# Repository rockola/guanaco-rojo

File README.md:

# guanaco-rojo
Guanaco Rojo PCB, yet another Red Llama clone

* v0.1: initial import, complete, unverified
* v0.2: pcb rerouted for 9 mm pots
* v0.3: SMD 4049 IC

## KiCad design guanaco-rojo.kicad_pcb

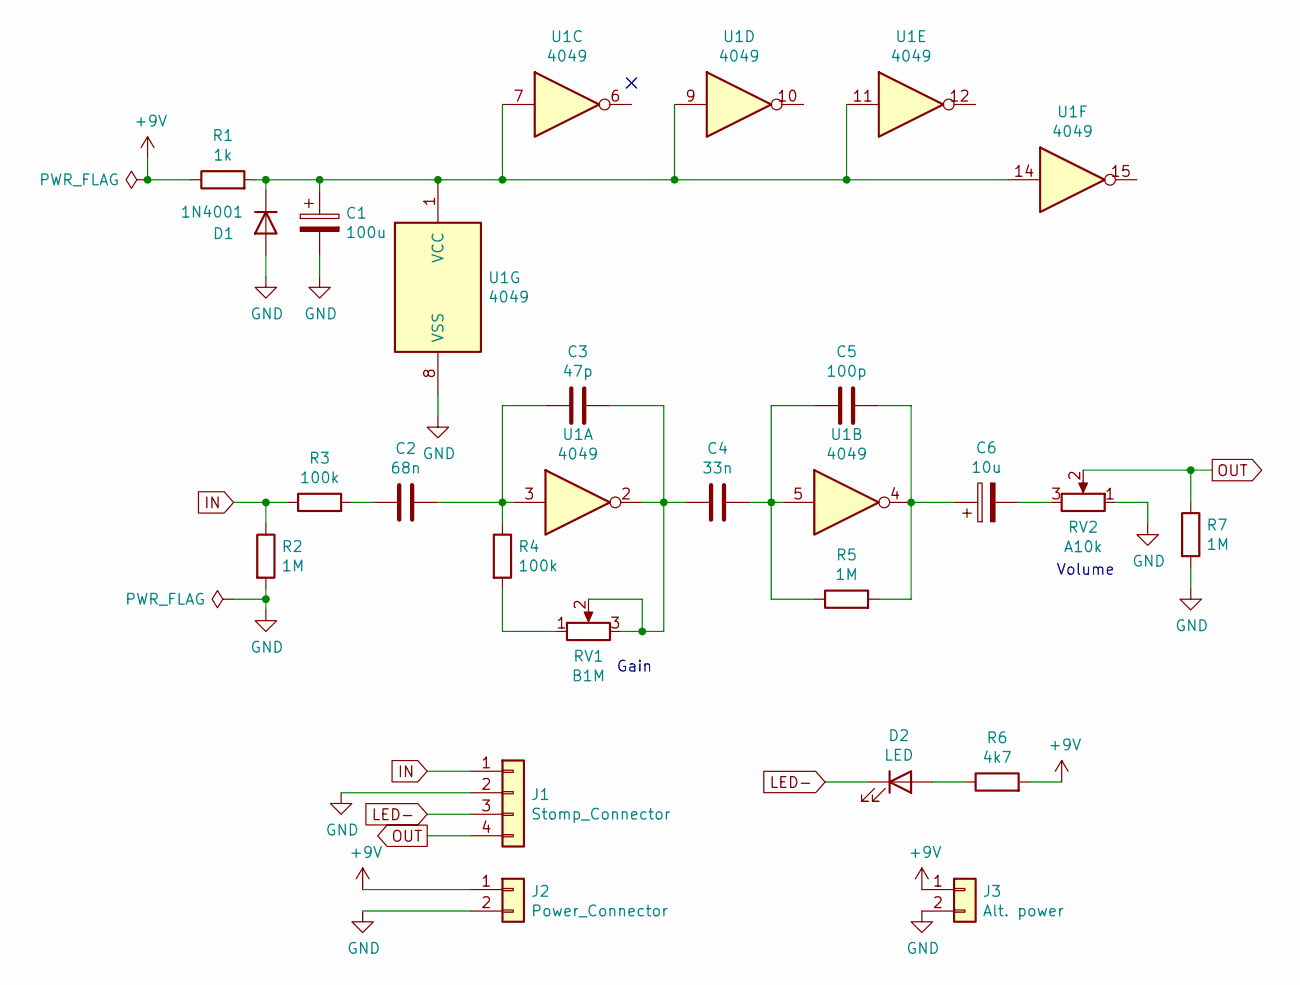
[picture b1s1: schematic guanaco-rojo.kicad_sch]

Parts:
C1: 100u; CP_Radial_D6.3mm_P2.50mm
C2: 68n; C_Rect_L7.0mm_W2.5mm_P5.00mm
C3: 47p; C_Disc_D5.0mm_W2.5mm_P5.00mm
C4: 33n; C_Rect_L7.0mm_W2.5mm_P5.00mm
C5: 100p; C_Disc_D5.0mm_W2.5mm_P5.00mm
C6: 10u; CP_Radial_D6.3mm_P2.50mm
D1: 1N4001; D_DO-41_SOD81_P7.62mm_Horizontal
D2: LED; LED_D5.0mm
J1: Stomp_Connector; Stomp_4pin
J2: Power_Connector; Power_Header_2pin_TOP
J3: Alt. power; Power_Header_2pin
R1: 1k; R_Axial_DIN0207_L6.3mm_D2.5mm_P7.62mm_Horizontal
R2, R5, R7: 1M; R_Axial_DIN0207_L6.3mm_D2.5mm_P7.62mm_Horizontal
R3, R4: 100k; R_Axial_DIN0207_L6.3mm_D2.5mm_P7.62mm_Horizontal
R6: 4k7; R_Axial_DIN0207_L6.3mm_D2.5mm_P7.62mm_Horizontal
RV1: B1M; 9MM_METAL_SHAFT
RV2: A10k; 9MM_METAL_SHAFT
U1: 4049; SOIC-16_3.9x9.9mm_P1.27mm

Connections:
+9V: J2.1 (PWR), J3.1 (PWR), R1.1, R6.2
GND: C1.2, D1.2 (A), J1.2 (GND), J2.2 (GND), J3.2 (GND), R2.2, R7.2, RV2.1, U1.8 (VSS)
IN: J1.1 (IN), R2.1, R3.1
LED-: D2.1 (K), J1.3 (SW)
unnamed: C1.1, D1.1 (K), R1.2, U1.1 (VCC), U1.7, U1.9, U1.11, U1.14
unnamed: C2.1, R3.2
unnamed: C2.2, C3.1, R4.1, U1.3
unnamed: C3.2, C4.1, RV1.2, RV1.3, U1.2
unnamed: C4.2, C5.1, R5.1, U1.5
unnamed: C5.2, C6.1, R5.2, U1.4
unnamed: C6.2, RV2.3
unnamed: D2.2 (A), R6.1
unnamed: R4.2, RV1.1
OUT: J1.4 (OUT), R7.1, RV2.2

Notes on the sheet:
Volume
Gain

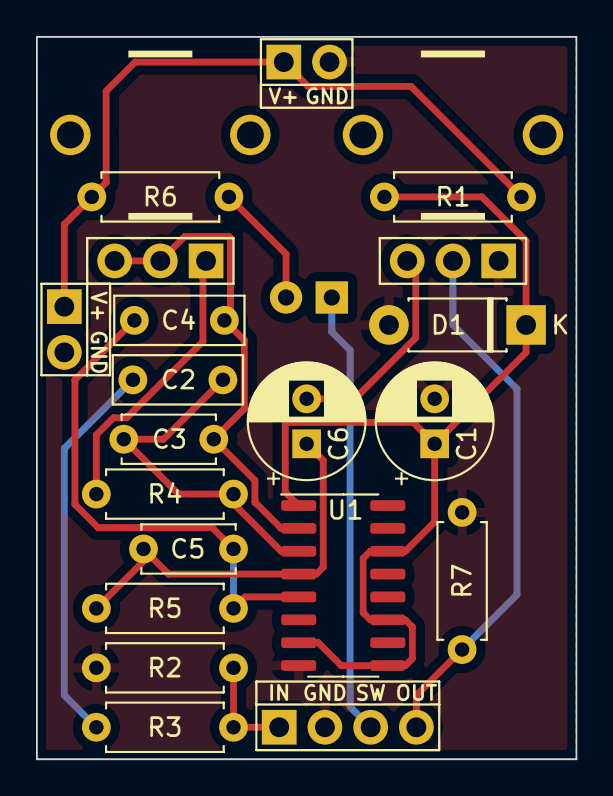
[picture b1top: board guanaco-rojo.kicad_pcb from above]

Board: 2 copper layers, 30.0 x 40.1 mm, 21 parts (1 on the bottom side), 14 nets.

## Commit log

2020-02-23 Added Emacs-specific ignores
2020-02-23 v0.1: initial import
2020-02-23 had copied over wrong file
2020-02-23 silkscreen markings
2020-03-11 v0.2: pcb rerouted for 9 mm pots, unverified
2020-03-11 v0.3: SMD 4049 IC
2020-03-11 v0.3
2020-03-11 v0.3 pcb images
2020-03-11 real v0.3 files
2020-03-11 PCB back and front images
2022-01-11 ignore backups directory
2022-01-11 updated to KiCad 6.0
